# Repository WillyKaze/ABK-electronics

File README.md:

```
____ ___  _  _    ____ _    ____ ____ ___ ____ ____ _  _ _ ____ ____ 
|__| |__] |_/  __ |___ |    |___ |     |  |__/ |  | |\ | | |    [__  
|  | |__] | \_    |___ |___ |___ |___  |  |  \ |__| | \| | |___ ___] 
                                                                      
```

# Abrakabuki electronics

This repo contains all necessary files to design and produce PCBs for the Abrakabuki product range.

## File format and folder structure

Documentation files should be in PDF. Board image files can be in PNG or PDF.

PCB Design file are in EAGLE Standard edition (7.4) file format.

These are general rules to help maintain a consistent folder structure:

* All libraries are placed inside the shared libraries repository. It can be found
  on [Github](https://github.com/exmchina-dev/eagle-resources)  

* One board for each project folder.  

* Mutiples revisions can be placed inside a subfolder. i.e. ECS-Board/Rev A1  

* BOMs, partlists, spreadsheet should placed inside a BOMs/ folder.  

* Documentations files are in eagle-resources/doc or in doc/ inside a project folder.

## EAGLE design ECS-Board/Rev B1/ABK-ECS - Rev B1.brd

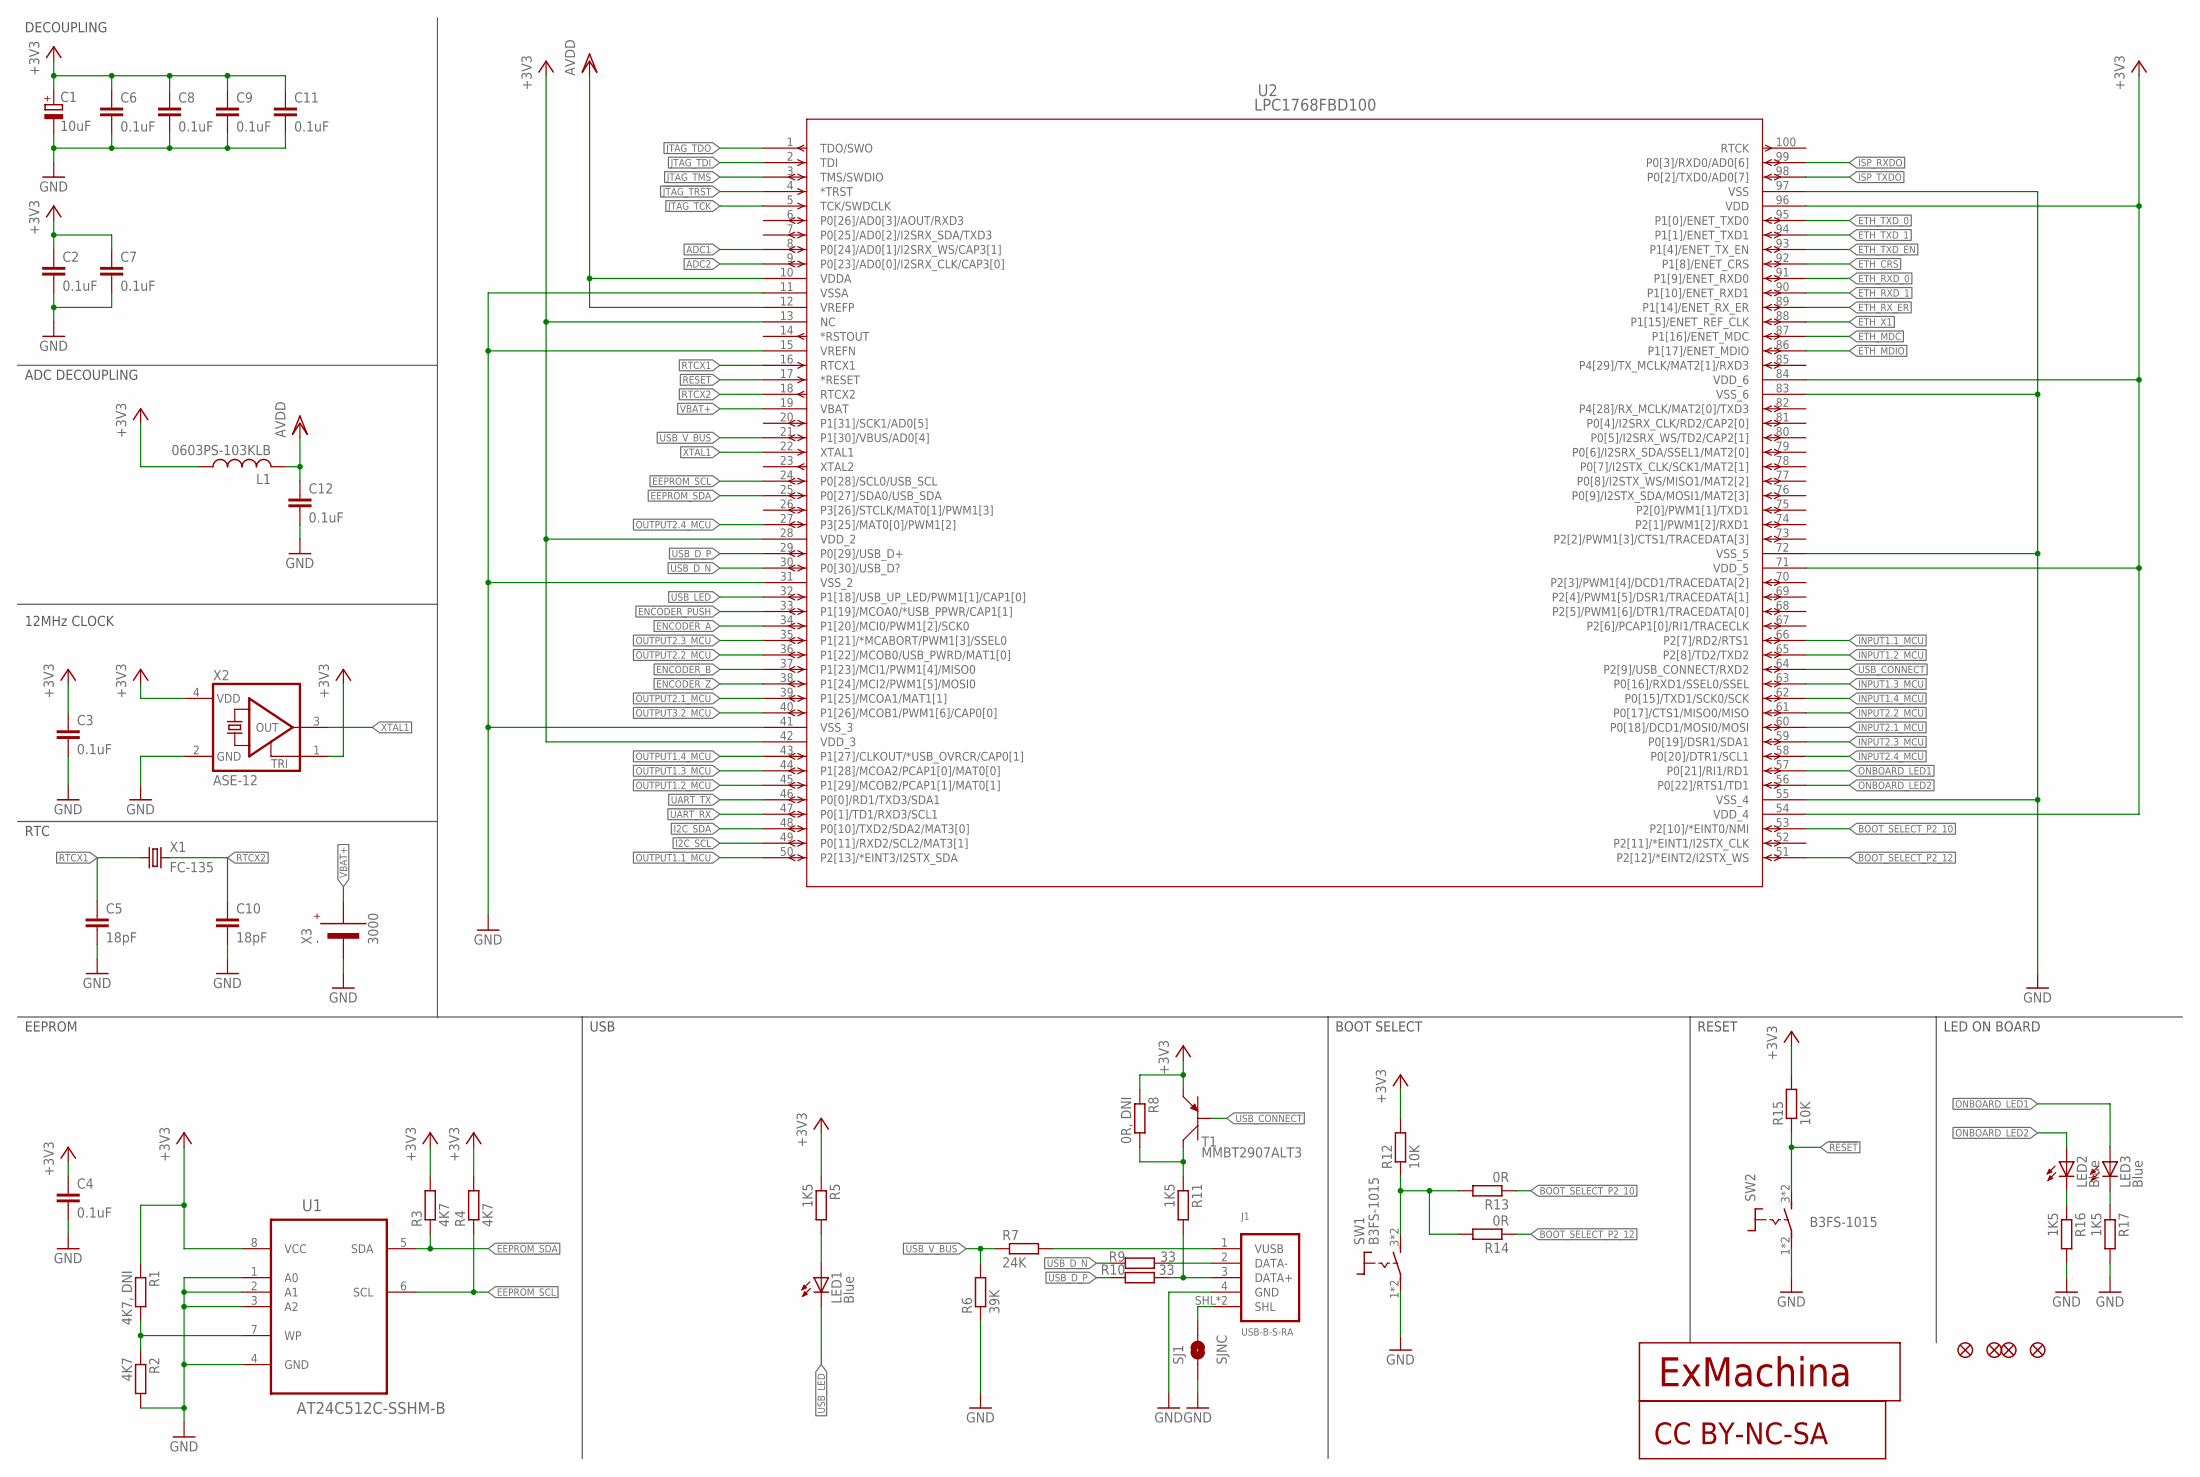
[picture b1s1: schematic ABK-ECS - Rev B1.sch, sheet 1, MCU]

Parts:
C1: 10uF; CT3216; MPN F931A106MAA
C2, C3, C4, C6, C7, C8, C9, C11, C12: 0.1uF; C0603; MPN MC0603B104K160CT
C5, C10: 18pF; C0603; MPN GRM1885C1H180JA01D
CC1: CC-BY-NC-SA
J1: USB-B-S-RA; MPN USB-B-S-RA
JP1, JP2, JP3, JP4: FIDUCIAL1X2; FIDUCIAL-1X2
L1: 0603PS-103KLB; 0603
LED1, LED2, LED3: Blue; CHIPLED_0603; MPN OVS-0603
R1: 4K7, DNI; R0603; MPN RC0603FR-074K7L
R2, R3, R4: 4K7; R0603; MPN RC0603FR-074K7L
R5, R11, R16, R17: 1K5; R0603; MPN RC0603FR-071K5L
R6: 39K; R0603
R7: 24K; R0603
R8: 0R, DNI; R0603; MPN RC0603FR-070RL
R9, R10: 33; R0603; MPN RC0603FR-0733RL
R12, R15: 10K; R0603; MPN RC0603FR-0710KL
R13, R14: 0R; R0603; MPN RC0603FR-070RL
SJ1: SJNC; SJ_2S
SW1, SW2: B3FS-1015; B3FS; MPN B3FS-1010
T1: MMBT2907ALT3; SOT−23
T2: EXMACHINA-LOGO-NAME; EXM-LOGO-BASELINE
U1: AT24C512C-SSHM-B; SOIC127P600X175-8N; MPN AT24C512C-SSHM-B
U2: LPC1768FBD100; SOT407-1; MPN LPC1768FBD100
X1: FC-135; MPN Q13FC13500004
X2: ASE-12; ASE; MPN ASE-12.000MHZ-LC-T
X3: 3000; MPN 3000

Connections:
!JTAG_TRST: U2.4 (*TRST)
!RESET: R15.1, SW2.3 (1), SW2.4 (1), U2.17 (*RESET); also elsewhere on the board
+3V3: C1.+, C2.1, C3.1, C4.1, C6.1, C7.1, C8.1, C9.1, C11.1, L1.P$1 (1), R1.1, R3.2, R4.2, R5.1, R8.1, R12.2, R15.2, T1.3 (C), U1.8 (VCC), U2.13 (NC), U2.28 (VDD_2), U2.42 (VDD_3), U2.54 (VDD_4), U2.71 (VDD_5), U2.84 (VDD_6), U2.96 (VDD), X2.1 (TRI), X2.4 (VDD); also elsewhere on the board
ADC1: U2.8 (P0[24]/AD0[1]/I2SRX_WS/CAP3[1]); also elsewhere on the board
ADC2: U2.9 (P0[23]/AD0[0]/I2SRX_CLK/CAP3[0]); also elsewhere on the board
AVDD: C12.1, L1.P$2 (2), U2.10 (VDDA), U2.12 (VREFP); also elsewhere on the board
BOOT_SELECT_P2_10: R13.1, U2.53 (P2[10]/*EINT0/NMI); also elsewhere on the board
BOOT_SELECT_P2_12: R14.1, U2.51 (P2[12]/*EINT2/I2STX_WS)
EEPROM_SCL: R4.1, U1.6 (SCL), U2.24 (P0[28]/SCL0/USB_SCL)
EEPROM_SDA: R3.1, U1.5 (SDA), U2.25 (P0[27]/SDA0/USB_SDA)
ENCODER_A: U2.34 (P1[20]/MCI0/PWM1[2]/SCK0); also elsewhere on the board
ENCODER_B: U2.37 (P1[23]/MCI1/PWM1[4]/MISO0); also elsewhere on the board
ENCODER_PUSH: U2.33 (P1[19]/MCOA0/*USB_PPWR/CAP1[1]); also elsewhere on the board
ENCODER_Z: U2.38 (P1[24]/MCI2/PWM1[5]/MOSI0); also elsewhere on the board
ETH_CRS: U2.92 (P1[8]/ENET_CRS); also elsewhere on the board
ETH_MDC: U2.87 (P1[16]/ENET_MDC); also elsewhere on the board
ETH_MDIO: U2.86 (P1[17]/ENET_MDIO); also elsewhere on the board
ETH_RXD_0: U2.91 (P1[9]/ENET_RXD0); also elsewhere on the board
ETH_RXD_1: U2.90 (P1[10]/ENET_RXD1); also elsewhere on the board
ETH_RX_ER: U2.89 (P1[14]/ENET_RX_ER); also elsewhere on the board
ETH_TXD_0: U2.95 (P1[0]/ENET_TXD0); also elsewhere on the board
ETH_TXD_1: U2.94 (P1[1]/ENET_TXD1); also elsewhere on the board
ETH_TXD_EN: U2.93 (P1[4]/ENET_TX_EN); also elsewhere on the board
ETH_X1: U2.88 (P1[15]/ENET_REF_CLK); also elsewhere on the board
GND: C1.-, C2.2, C3.2, C4.2, C5.2, C6.2, C7.2, C8.2, C9.2, C10.2, C11.2, C12.2, J1.4 (GND), R2.2, R6.1, R16.2, R17.2, SJ1.1, SW1.1 (2), SW1.2, SW2.1 (2), SW2.2, U1.1 (A0), U1.2 (A1), U1.3 (A2), U1.4 (GND), U2.11 (VSSA), U2.15 (VREFN), U2.31 (VSS_2), U2.41 (VSS_3), U2.55 (VSS_4), U2.72 (VSS_5), U2.83 (VSS_6), U2.97 (VSS), X2.2 (GND), X3.- (VBAT-); also elsewhere on the board
I2C_SCL: U2.49 (P0[11]/RXD2/SCL2/MAT3[1]); also elsewhere on the board
I2C_SDA: U2.48 (P0[10]/TXD2/SDA2/MAT3[0]); also elsewhere on the board
INPUT1.1_MCU: U2.66 (P2[7]/RD2/RTS1); also elsewhere on the board
INPUT1.2_MCU: U2.65 (P2[8]/TD2/TXD2); also elsewhere on the board
INPUT1.3_MCU: U2.63 (P0[16]/RXD1/SSEL0/SSEL); also elsewhere on the board
INPUT1.4_MCU: U2.62 (P0[15]/TXD1/SCK0/SCK); also elsewhere on the board
INPUT2.1_MCU: U2.60 (P0[18]/DCD1/MOSI0/MOSI); also elsewhere on the board
INPUT2.2_MCU: U2.61 (P0[17]/CTS1/MISO0/MISO); also elsewhere on the board
INPUT2.3_MCU: U2.59 (P0[19]/DSR1/SDA1); also elsewhere on the board
INPUT2.4_MCU: U2.58 (P0[20]/DTR1/SCL1); also elsewhere on the board
ISP_RXDO: U2.99 (P0[3]/RXD0/AD0[6]); also elsewhere on the board
ISP_TXDO: U2.98 (P0[2]/TXD0/AD0[7]); also elsewhere on the board
JTAG_TCK: U2.5 (TCK/SWDCLK); also elsewhere on the board
JTAG_TDI: U2.2 (TDI); also elsewhere on the board
JTAG_TDO: U2.1 (TDO/SWO); also elsewhere on the board
JTAG_TMS: U2.3 (TMS/SWDIO); also elsewhere on the board
unnamed: J1.3 (DATA+), R10.1, R11.2
unnamed: J1.2 (DATA-), R9.1
unnamed: LED3.C, R17.1
unnamed: R12.1, R13.2, R14.2, SW1.3 (1), SW1.4 (1)
unnamed: R1.2, R2.1, U1.7 (WP)
unnamed: LED1.A, R5.2
unnamed: LED2.C, R16.1
unnamed: R8.2, R11.1, T1.2 (E)
unnamed: J1.SHL, J1.SHL1 (SHL), SJ1.2
unnamed: J1.1 (VUSB), R7.2
ONBOARD_LED1: LED3.A, U2.57 (P0[21]/RI1/RD1)
ONBOARD_LED2: LED2.A, U2.56 (P0[22]/RTS1/TD1)
OUTPUT1.1_MCU: U2.50 (P2[13]/*EINT3/I2STX_SDA); also elsewhere on the board
OUTPUT1.2_MCU: U2.45 (P1[29]/MCOB2/PCAP1[1]/MAT0[1]); also elsewhere on the board
OUTPUT1.3_MCU: U2.44 (P1[28]/MCOA2/PCAP1[0]/MAT0[0]); also elsewhere on the board
OUTPUT1.4_MCU: U2.43 (P1[27]/CLKOUT/*USB_OVRCR/CAP0[1]); also elsewhere on the board
OUTPUT2.1_MCU: U2.39 (P1[25]/MCOA1/MAT1[1]); also elsewhere on the board
OUTPUT2.2_MCU: U2.36 (P1[22]/MCOB0/USB_PWRD/MAT1[0]); also elsewhere on the board
OUTPUT2.3_MCU: U2.35 (P1[21]/*MCABORT/PWM1[3]/SSEL0); also elsewhere on the board
OUTPUT2.4_MCU: U2.27 (P3[25]/MAT0[0]/PWM1[2]); also elsewhere on the board
OUTPUT3.2_MCU: U2.40 (P1[26]/MCOB1/PWM1[6]/CAP0[0]); also elsewhere on the board
RTCX1: C5.1, U2.16 (RTCX1), X1.1
RTCX2: C10.1, U2.18 (RTCX2), X1.2
UART_RX: U2.47 (P0[1]/TD1/RXD3/SCL1); also elsewhere on the board
UART_TX: U2.46 (P0[0]/RD1/TXD3/SDA1); also elsewhere on the board
USB_CONNECT: T1.1 (B), U2.64 (P2[9]/USB_CONNECT/RXD2)
USB_D_N: R9.2, U2.30 (P0[30]/USB_D?)
USB_D_P: R10.2, U2.29 (P0[29]/USB_D+)
USB_LED: LED1.C, U2.32 (P1[18]/USB_UP_LED/PWM1[1]/CAP1[0])
USB_V_BUS: R6.2, R7.1, U2.21 (P1[30]/VBUS/AD0[4])
VBAT+: U2.19 (VBAT), X3.+1 (VBAT+), X3.+2 (VBAT+)
XTAL1: U2.22 (XTAL1), X2.3 (OUT)

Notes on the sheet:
USB
BOOT SELECT
LED ON BOARD
RESET
EEPROM
RTC
12MHz CLOCK
DECOUPLING
ADC DECOUPLING

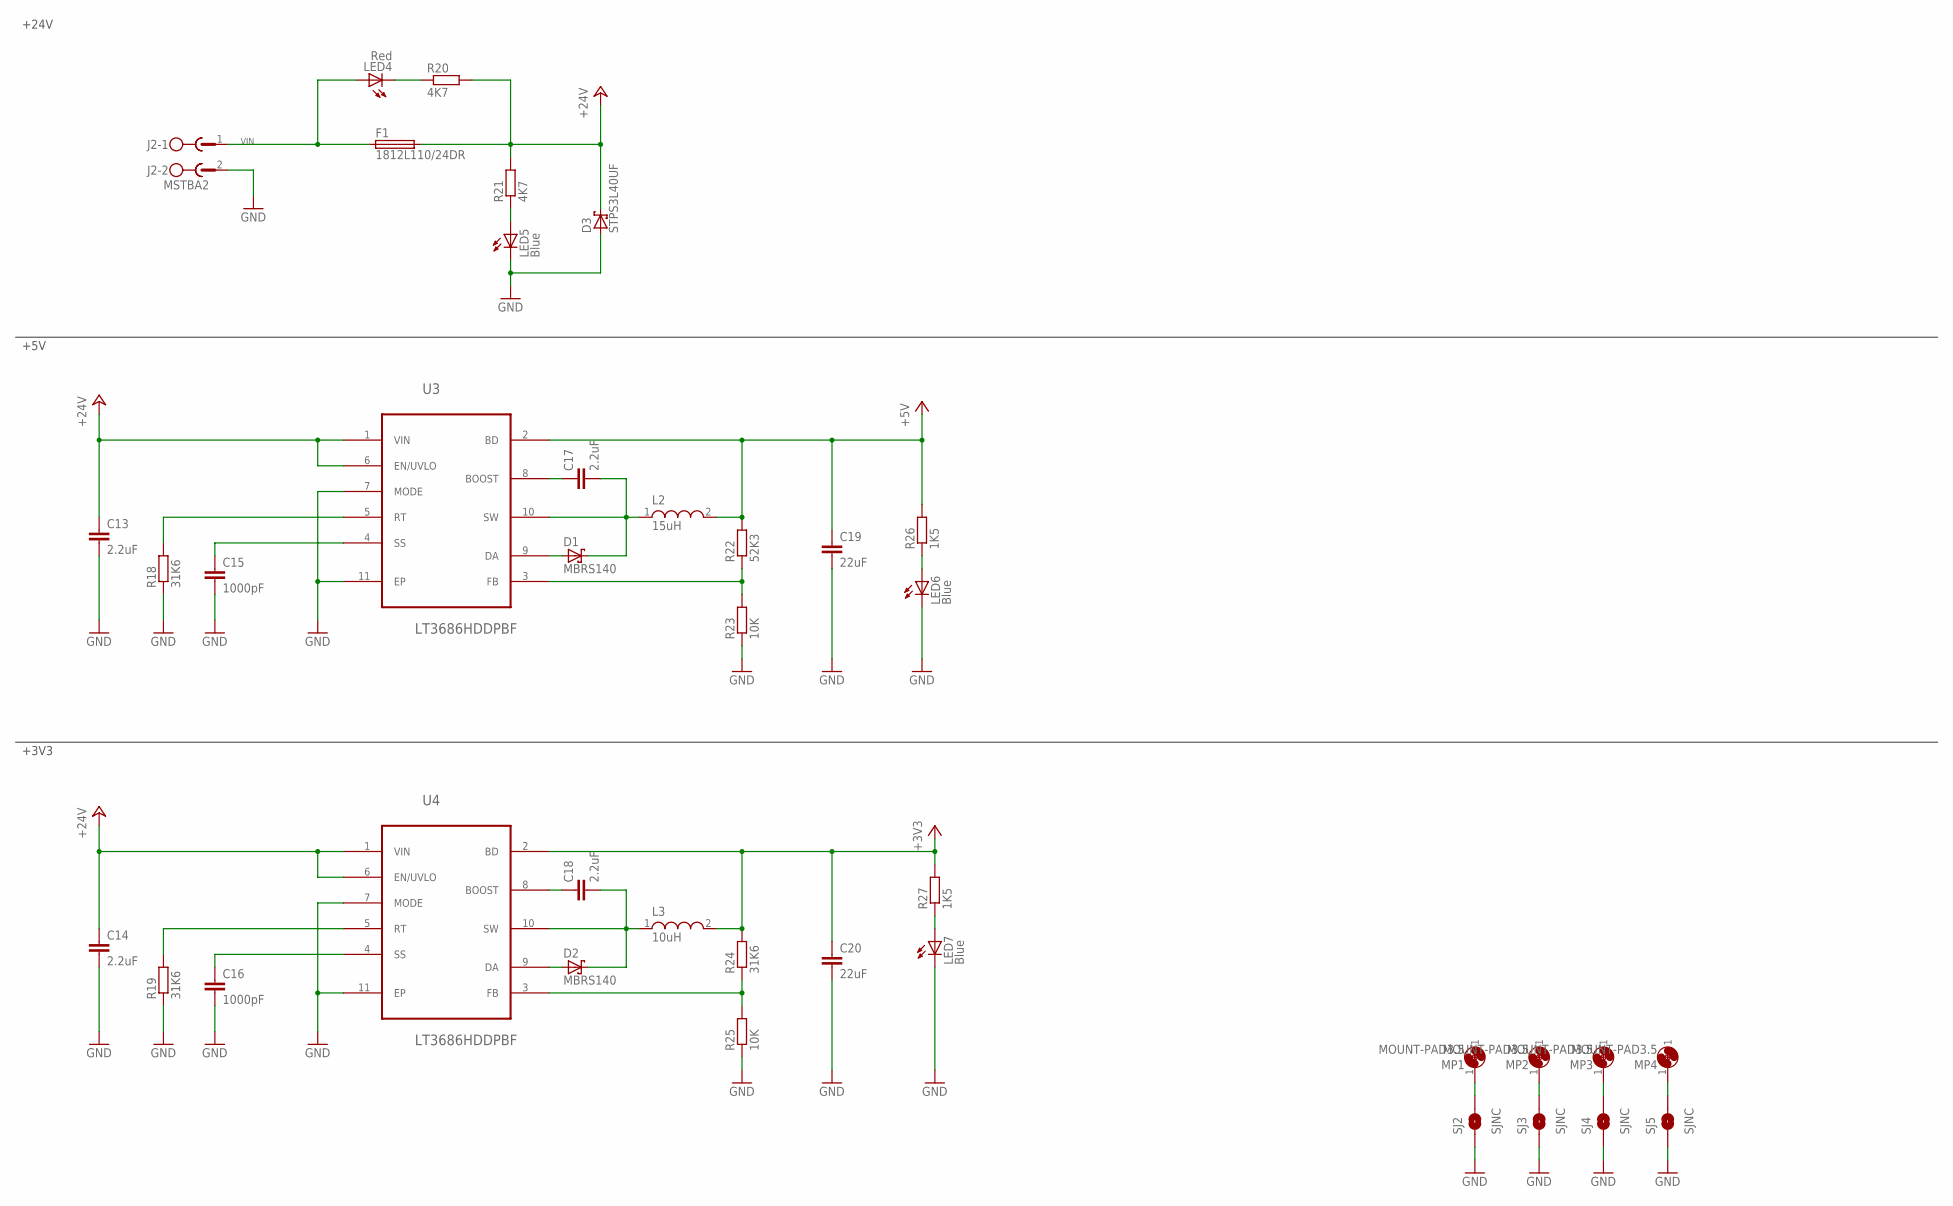
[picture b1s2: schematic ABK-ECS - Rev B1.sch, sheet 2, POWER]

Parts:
C13, C14, C17, C18: 2.2uF; C0603; MPN GRT188R61H225KE13D
C15, C16: 1000pF; C0603; MPN GRM188R71H102KA01D
C19, C20: 22uF; C0805; MPN C0805C226M9PACTU
D1, D2: MBRS140; DO-214AA; MPN MBRS140T3G
D3: STPS3L40UF; SMB
F1: 1812L110/24DR; LITTLEFUSE_SMD; MPN 3557
J2: MSTBA2
L2: 15uH; WE-PD2_5848/5820; MPN 744774115
L3: 10uH; WE-PD2_5848/5820; MPN 74477410
LED4: Red; CHIPLED_0603; MPN OVS-0608
LED5, LED6, LED7: Blue; CHIPLED_0603; MPN OVS-0603
MP1, MP2, MP3, MP4: MOUNT-PAD3.5; P3,5
R18, R19, R24: 31K6; R0603; MPN MCMR06X3162FTL
R20, R21: 4K7; R0603; MPN RC0603FR-074K7L
R22: 52K3; R0603; MPN MC0063W0603152K3
R23, R25: 10K; R0603; MPN RC0603FR-0710KL
R26, R27: 1K5; R0603; MPN RC0603FR-071K5L
SJ2, SJ3, SJ4, SJ5: SJNC; SJ_2S
U3, U4: LT3686HDDPBF; DFN300X300X80-11N

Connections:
1: MP1.1, SJ2.2
2: MP2.1, SJ3.2
3: MP3.1, SJ4.2
4: MP4.1, SJ5.2
+3V3: C20.1, L3.2, R24.2, R27.2, U4.2 (BD); also elsewhere on the board
+5V: C19.1, L2.2, R22.2, R26.2, U3.2 (BD); also elsewhere on the board
+24V: C13.1, C14.1, D3.C, F1.2, R20.2, R21.2, U3.1 (VIN), U3.6 (EN/UVLO), U4.1 (VIN), U4.6 (EN/UVLO); also elsewhere on the board
GND: C13.2, C14.2, C15.2, C16.2, C19.2, C20.2, D3.A, J2.2, LED5.C, LED6.C, LED7.C, R18.1, R19.1, R23.1, R25.1, SJ2.1, SJ3.1, SJ4.1, SJ5.1, U3.7 (MODE), U3.11 (EP), U4.7 (MODE), U4.11 (EP); also elsewhere on the board
unnamed: R18.2, U3.5 (RT)
unnamed: C15.1, U3.4 (SS)
unnamed: R19.2, U4.5 (RT)
unnamed: C16.1, U4.4 (SS)
unnamed: R22.1, R23.2, U3.3 (FB)
unnamed: C17.1, U3.8 (BOOST)
unnamed: C17.2, D1.C, L2.1, U3.10 (SW)
unnamed: D1.A, U3.9 (DA)
unnamed: R24.1, R25.2, U4.3 (FB)
unnamed: C18.1, U4.8 (BOOST)
unnamed: C18.2, D2.C, L3.1, U4.10 (SW)
unnamed: D2.A, U4.9 (DA)
unnamed: LED5.A, R21.1
unnamed: LED4.C, R20.1
unnamed: LED7.A, R27.1
unnamed: LED6.A, R26.1
VIN: F1.1, J2.1, LED4.A

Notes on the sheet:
+5V
+3V3
+24V

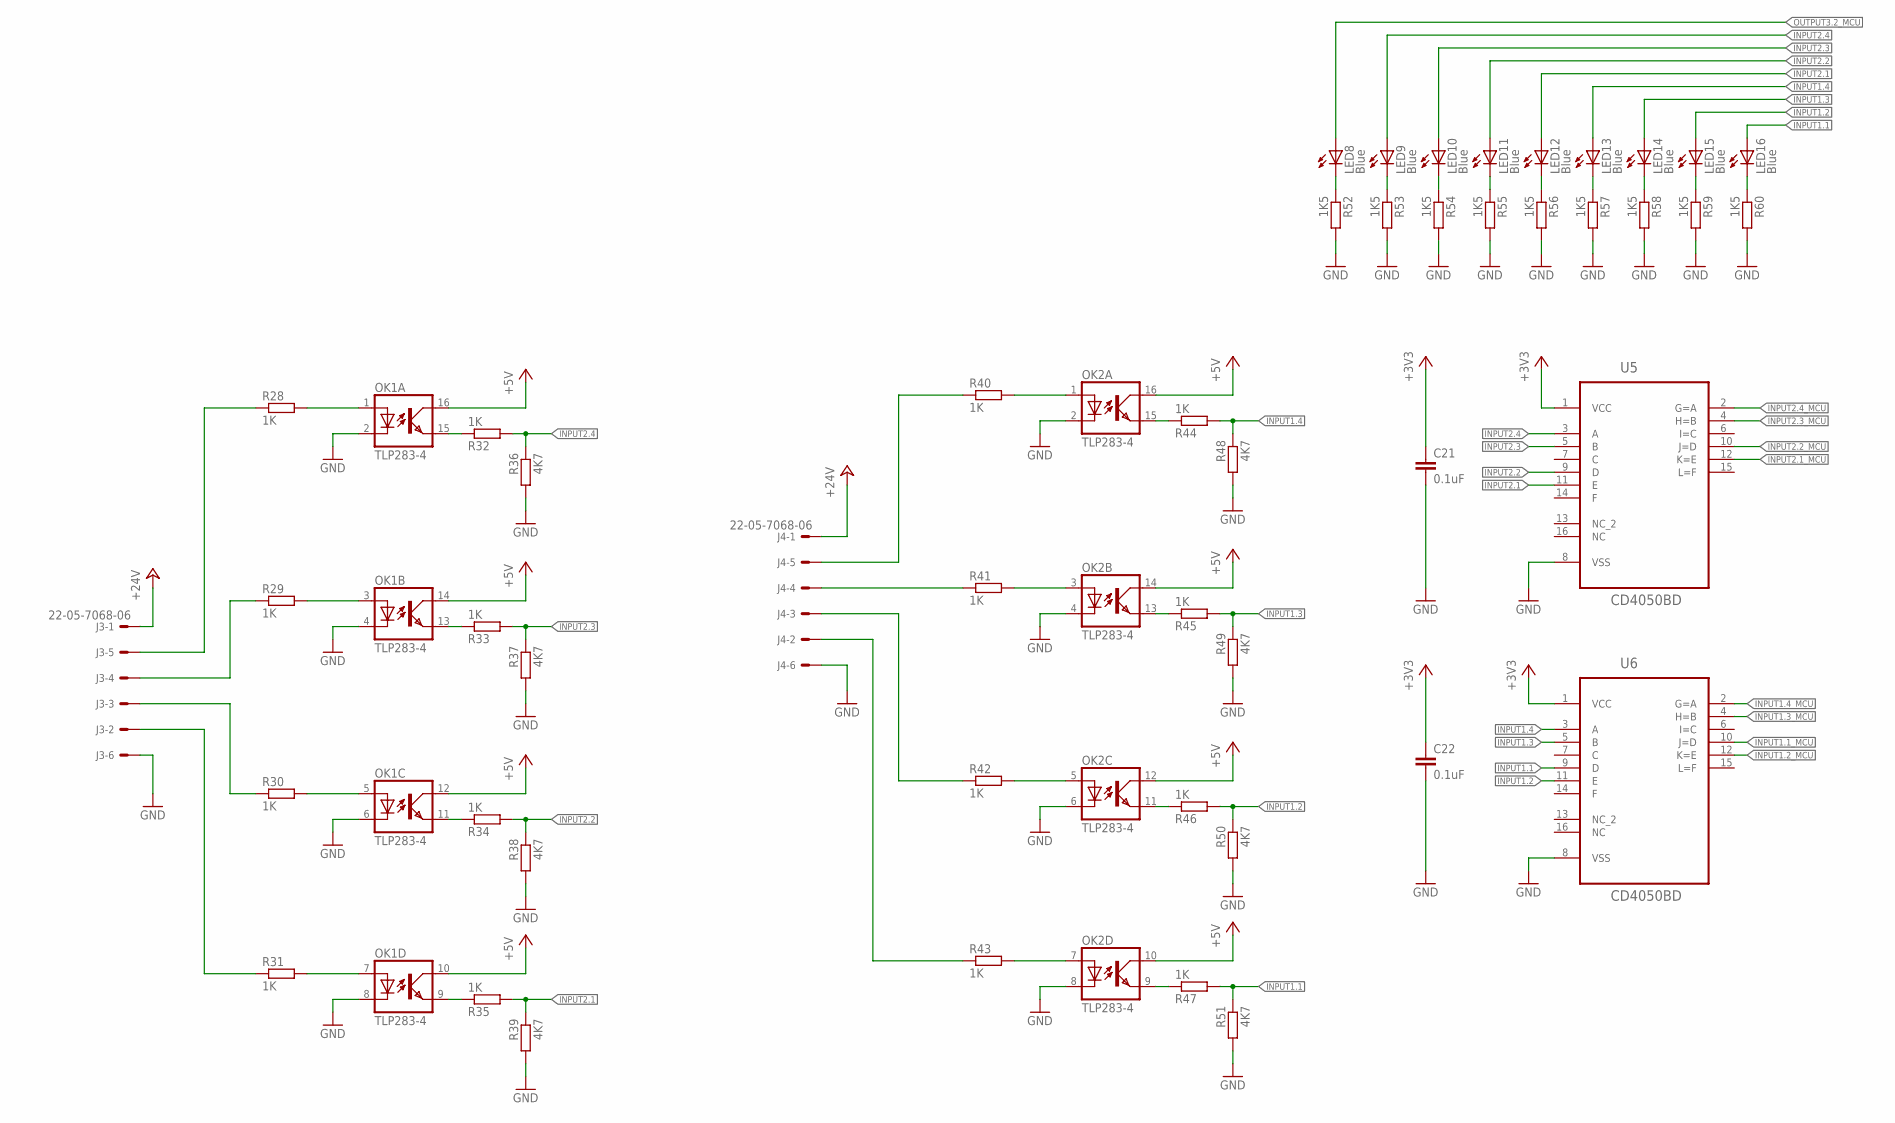
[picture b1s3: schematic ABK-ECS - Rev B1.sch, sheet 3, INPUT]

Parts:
C21, C22: 0.1uF; C0603; MPN MC0603B104K160CT
J3, J4: 22-05-7068-06; 7395-06
LED8, LED9, LED10, LED11, LED12, LED13, LED14, LED15, LED16: Blue; CHIPLED_0603; MPN OVS-0603
OK1, OK2: TLP283-4; MINI-FLAT-16; MPN TCMT4100
R28, R29, R30, R31, R32, R33, R34, R35, R40, R41, R42, R43, R44, R45, R46, R47: 1K; R0603; MPN RC0603FR-071KL
R36, R37, R38, R39, R48, R49, R50, R51: 4K7; R0603; MPN RC0603FR-074K7L
R52, R53, R54, R55, R56, R57, R58, R59, R60: 1K5; R0603; MPN RC0603FR-071K5L
U5, U6: CD4050BD; SOIC127P600X175-16N

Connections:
+3V3: C21.1, C22.1, U5.1 (VCC), U6.1 (VCC); also elsewhere on the board
+5V: OK1.10 (COL), OK1.12 (COL), OK1.14 (COL), OK1.16 (COL), OK2.10 (COL), OK2.12 (COL), OK2.14 (COL), OK2.16 (COL); also elsewhere on the board
+24V: J3.1, J4.1; also elsewhere on the board
GND: C21.2, C22.2, J3.6, J4.6, OK1.2 (C), OK1.4 (C), OK1.6 (C), OK1.8 (C), OK2.2 (C), OK2.4 (C), OK2.6 (C), OK2.8 (C), R36.2, R37.2, R38.2, R39.2, R48.2, R49.2, R50.2, R51.2, R52.2, R53.2, R54.2, R55.2, R56.2, R57.2, R58.2, R59.2, R60.2, U5.8 (VSS), U6.8 (VSS); also elsewhere on the board
INPUT1.1: LED16.A, R47.2, R51.1, U6.9 (D)
INPUT1.1_MCU: U6.10 (J=D); also elsewhere on the board
INPUT1.2: LED15.A, R46.2, R50.1, U6.11 (E)
INPUT1.2_MCU: U6.12 (K=E); also elsewhere on the board
INPUT1.3: LED14.A, R45.2, R49.1, U6.5 (B)
INPUT1.3_MCU: U6.4 (H=B); also elsewhere on the board
INPUT1.4: LED13.A, R44.2, R48.1, U6.3 (A)
INPUT1.4_MCU: U6.2 (G=A); also elsewhere on the board
INPUT2.1: LED12.A, R35.2, R39.1, U5.11 (E)
INPUT2.1_MCU: U5.12 (K=E); also elsewhere on the board
INPUT2.2: LED11.A, R34.2, R38.1, U5.9 (D)
INPUT2.2_MCU: U5.10 (J=D); also elsewhere on the board
INPUT2.3: LED10.A, R33.2, R37.1, U5.5 (B)
INPUT2.3_MCU: U5.4 (H=B); also elsewhere on the board
INPUT2.4: LED9.A, R32.2, R36.1, U5.3 (A)
INPUT2.4_MCU: U5.2 (G=A); also elsewhere on the board
unnamed: OK1.1 (A), R28.2
unnamed: OK1.3 (A), R29.2
unnamed: OK1.5 (A), R30.2
unnamed: OK1.7 (A), R31.2
unnamed: J3.2, R31.1
unnamed: J3.3, R30.1
unnamed: J3.4, R29.1
unnamed: J3.5, R28.1
unnamed: LED8.C, R52.1
unnamed: LED9.C, R53.1
unnamed: LED10.C, R54.1
unnamed: LED11.C, R55.1
unnamed: OK1.9 (EMIT), R35.1
unnamed: OK1.11 (EMIT), R34.1
unnamed: OK1.13 (EMIT), R33.1
unnamed: OK1.15 (EMIT), R32.1
unnamed: LED12.C, R56.1
unnamed: OK2.1 (A), R40.2
unnamed: J4.5, R40.1
unnamed: LED16.C, R60.1
unnamed: OK2.15 (EMIT), R44.1
unnamed: OK2.3 (A), R41.2
unnamed: J4.4, R41.1
unnamed: OK2.13 (EMIT), R45.1
unnamed: OK2.5 (A), R42.2
unnamed: J4.3, R42.1
unnamed: OK2.11 (EMIT), R46.1
unnamed: LED13.C, R57.1
unnamed: LED14.C, R58.1
unnamed: LED15.C, R59.1
unnamed: OK2.9 (EMIT), R47.1
unnamed: OK2.7 (A), R43.2
unnamed: J4.2, R43.1
OUTPUT3.2_MCU: LED8.A; also elsewhere on the board

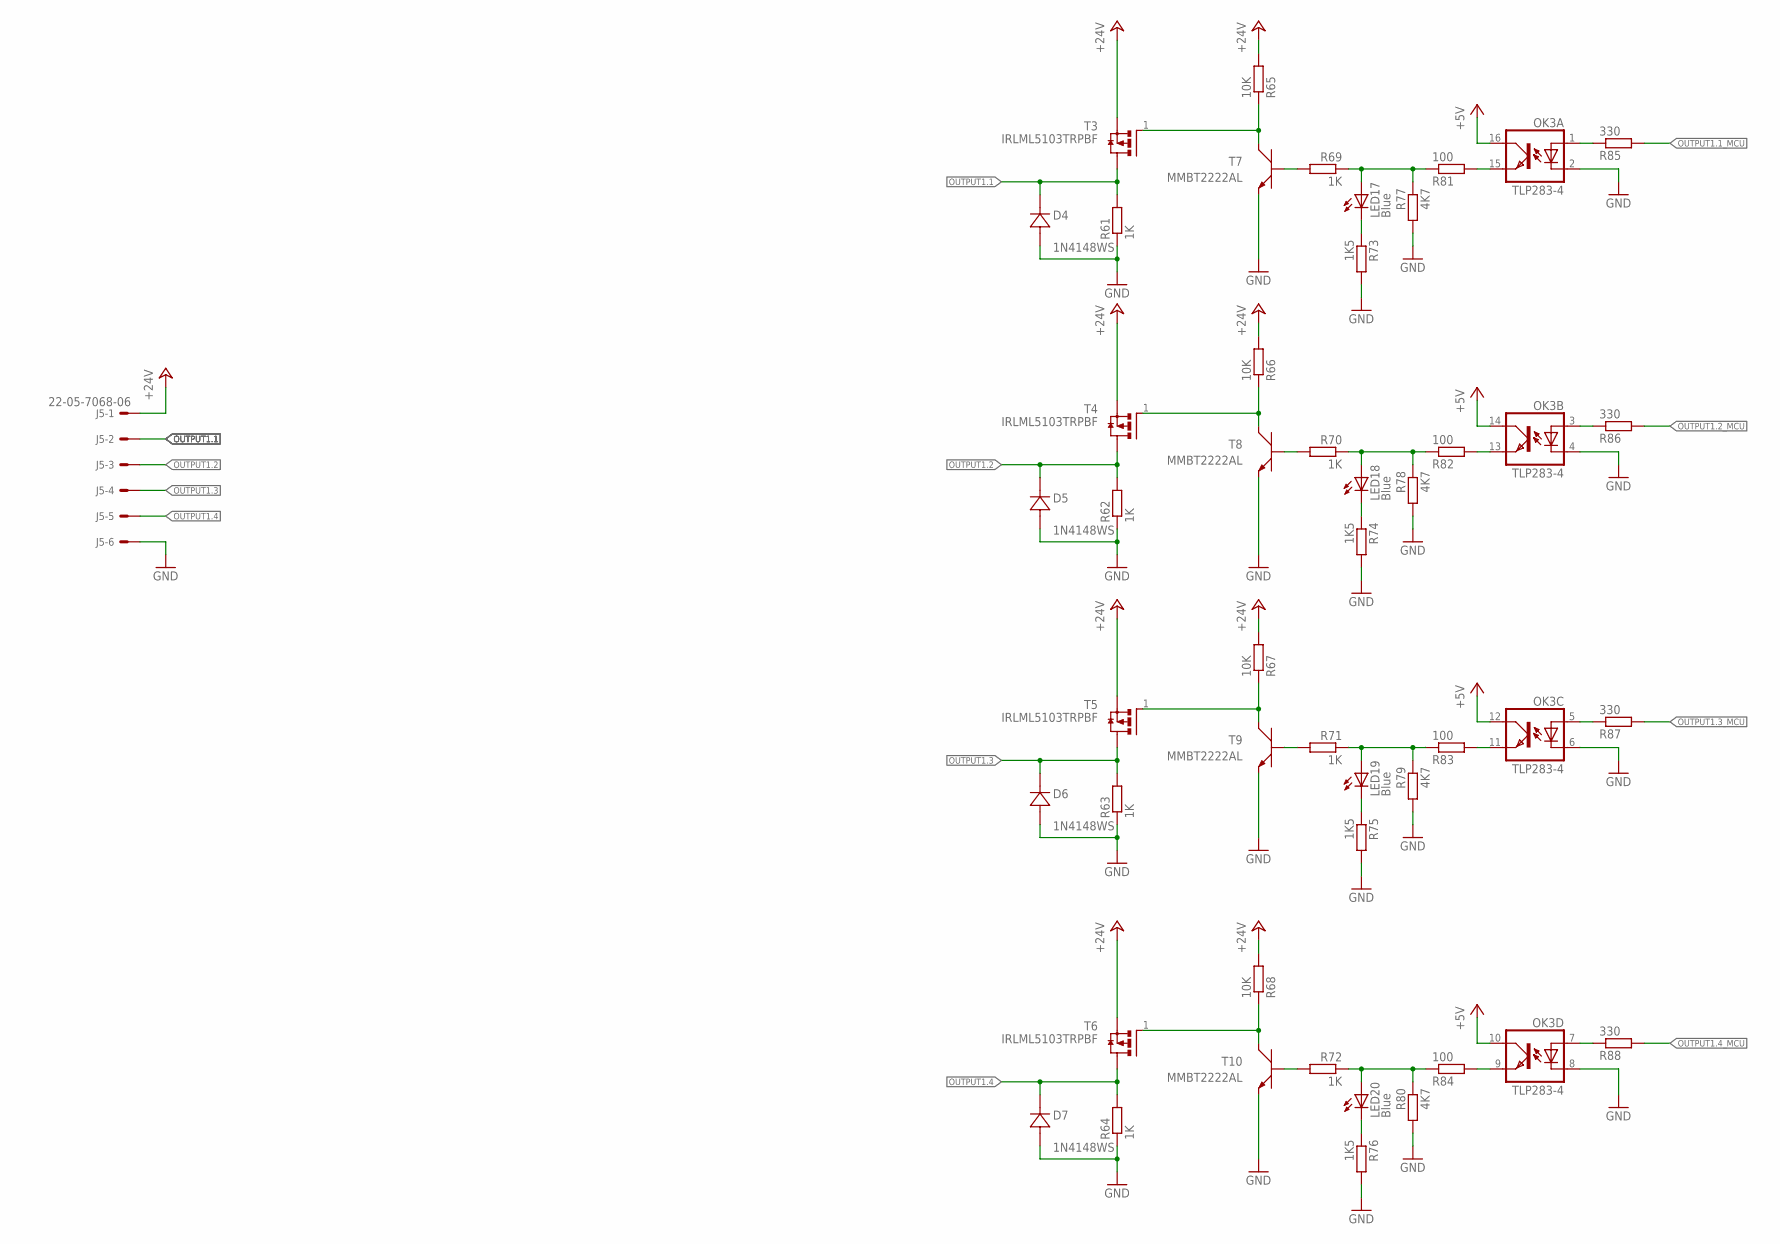
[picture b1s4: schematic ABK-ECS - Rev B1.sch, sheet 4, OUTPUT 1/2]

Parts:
D4, D5, D6, D7: 1N4148WS; SOD323-W; MPN 1N4148WS
J5: 22-05-7068-06; 7395-06
LED17, LED18, LED19, LED20: Blue; CHIPLED_0603; MPN OVS-0603
OK3: TLP283-4; MINI-FLAT-16; MPN TCMT4100
R61, R62, R63, R64: 1K; R1206
R65, R66, R67, R68: 10K; R0603; MPN RC0603FR-0710KL
R69, R70, R71, R72: 1K; R0603; MPN RC0603FR-071KL
R73, R74, R75, R76: 1K5; R0603; MPN RC0603FR-071K5L
R77, R78, R79, R80: 4K7; R0603; MPN RC0603FR-074K7L
R81, R82, R83, R84: 100; R0603; MPN RC0603FR-13100RL
R85, R86, R87, R88: 330; R0603; MPN RC0603FR-07330RL
T3, T4, T5, T6: IRLML5103TRPBF; SOT95P240X112-3N; MPN IRLML5103TRPBF
T7, T8, T9, T10: MMBT2222AL; SOT−23; MPN MMBT2222ALT1G

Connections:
+5V: OK3.10 (COL), OK3.12 (COL), OK3.14 (COL), OK3.16 (COL); also elsewhere on the board
+24V: J5.1, R65.2, R66.2, R67.2, R68.2, T3.2 (S), T4.2 (S), T5.2 (S), T6.2 (S); also elsewhere on the board
GND: D4.A (2), D5.A (2), D6.A (2), D7.A (2), J5.6, OK3.2 (C), OK3.4 (C), OK3.6 (C), OK3.8 (C), R61.1, R62.1, R63.1, R64.1, R73.2, R74.2, R75.2, R76.2, R77.2, R78.2, R79.2, R80.2, T7.2 (E), T8.2 (E), T9.2 (E), T10.2 (E); also elsewhere on the board
unnamed: LED17.A, R69.1, R77.1, R81.1
unnamed: OK3.15 (EMIT), R81.2
unnamed: LED18.A, R70.1, R78.1, R82.1
unnamed: OK3.13 (EMIT), R82.2
unnamed: LED19.A, R71.1, R79.1, R83.1
unnamed: LED20.A, R72.1, R80.1, R84.1
unnamed: OK3.11 (EMIT), R83.2
unnamed: OK3.9 (EMIT), R84.2
unnamed: OK3.1 (A), R85.1
unnamed: OK3.3 (A), R86.1
unnamed: OK3.7 (A), R88.1
unnamed: OK3.5 (A), R87.1
unnamed: LED17.C, R73.1
unnamed: LED18.C, R74.1
unnamed: LED19.C, R75.1
unnamed: LED20.C, R76.1
unnamed: R65.1, T3.1 (G), T7.3 (C)
unnamed: R66.1, T4.1 (G), T8.3 (C)
unnamed: R67.1, T5.1 (G), T9.3 (C)
unnamed: R68.1, T6.1 (G), T10.3 (C)
unnamed: R69.2, T7.1 (B)
unnamed: R70.2, T8.1 (B)
unnamed: R71.2, T9.1 (B)
unnamed: R72.2, T10.1 (B)
OUTPUT1.1: D4.C (1), J5.2, R61.2, T3.3 (D)
OUTPUT1.1_MCU: R85.2; also elsewhere on the board
OUTPUT1.2: D5.C (1), J5.3, R62.2, T4.3 (D)
OUTPUT1.2_MCU: R86.2; also elsewhere on the board
OUTPUT1.3: D6.C (1), J5.4, R63.2, T5.3 (D)
OUTPUT1.3_MCU: R87.2; also elsewhere on the board
OUTPUT1.4: D7.C (1), J5.5, R64.2, T6.3 (D)
OUTPUT1.4_MCU: R88.2; also elsewhere on the board

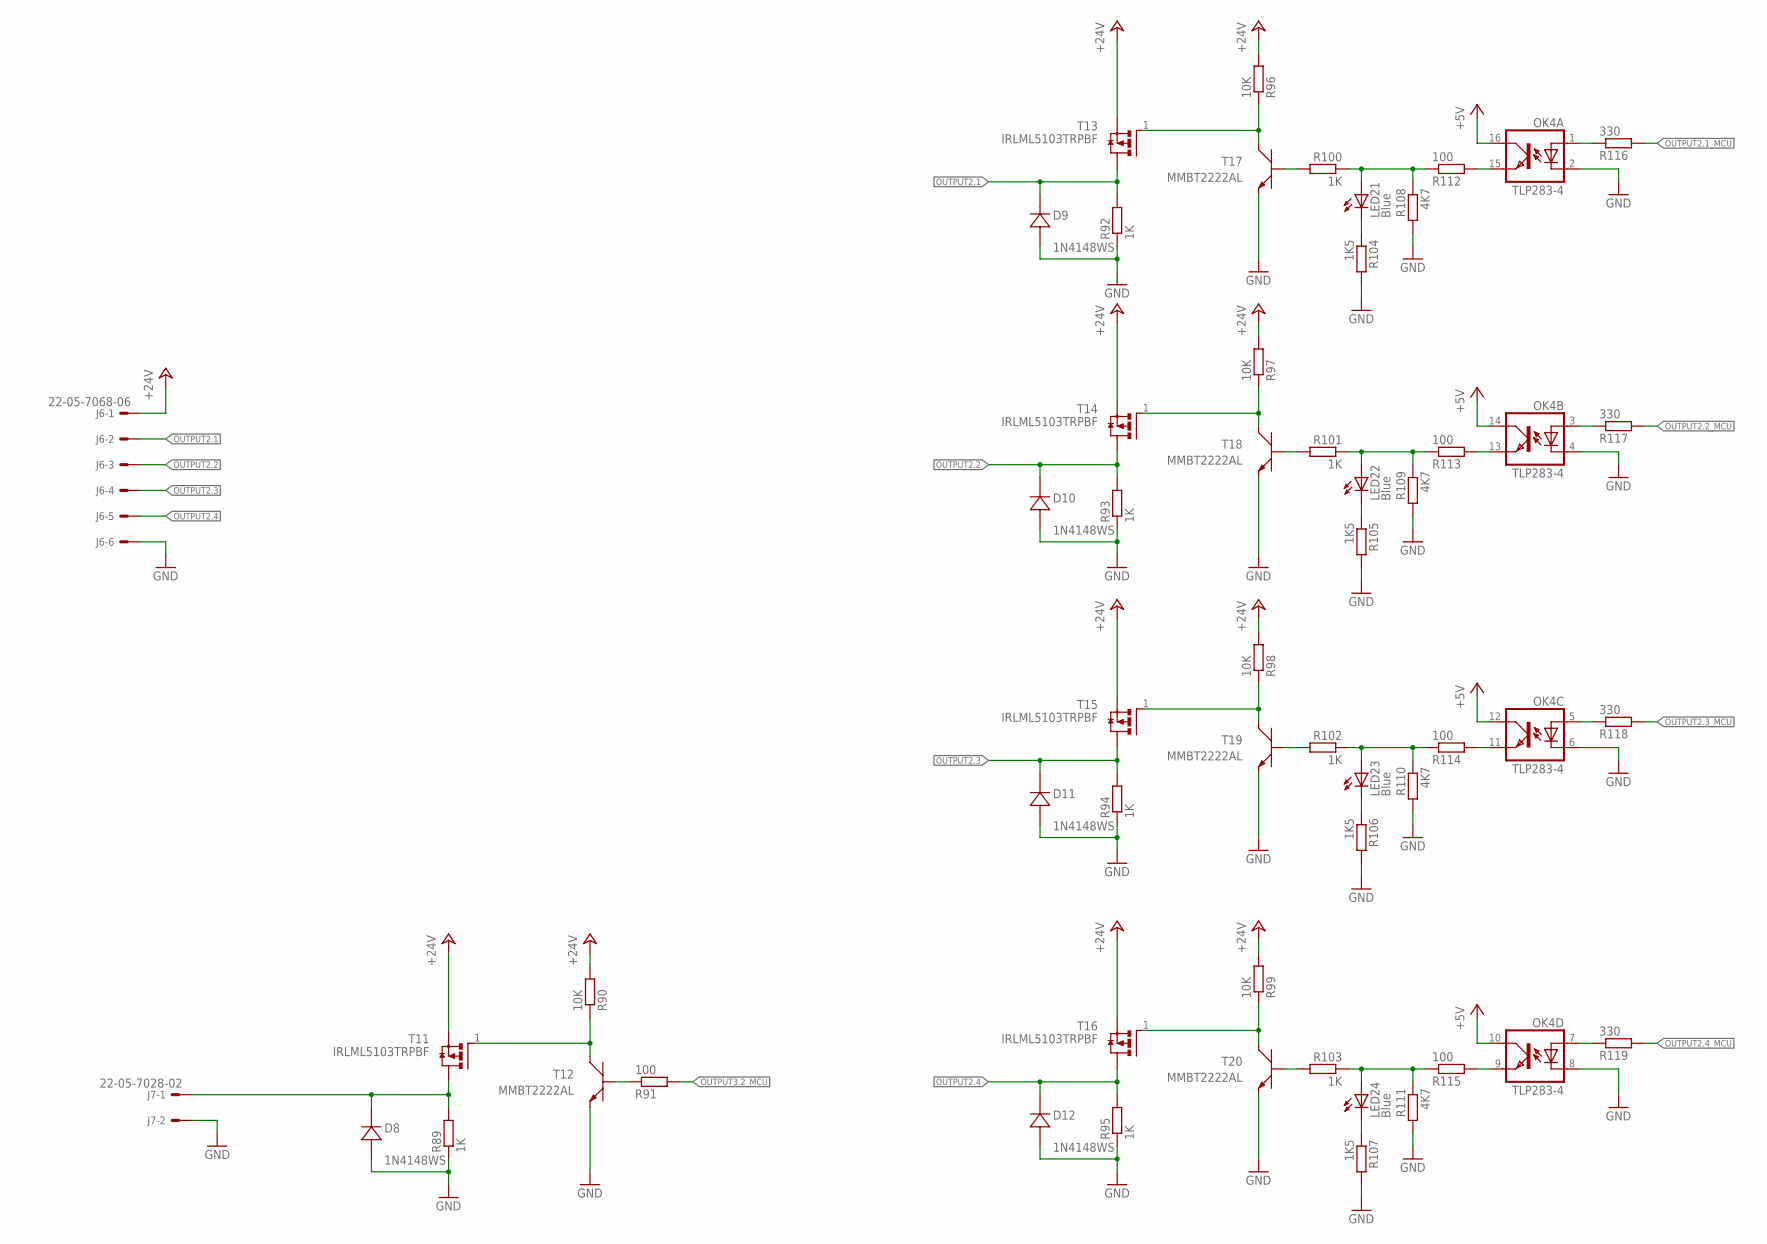
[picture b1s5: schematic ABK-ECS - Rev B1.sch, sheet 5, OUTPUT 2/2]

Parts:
D8, D9, D10, D11, D12: 1N4148WS; SOD323-W; MPN 1N4148WS
J6: 22-05-7068-06; 7395-06
J7: 22-05-7028-02; 7395-02; MPN 22-05-7028
LED21, LED22, LED23, LED24: Blue; CHIPLED_0603; MPN OVS-0603
OK4: TLP283-4; MINI-FLAT-16; MPN TCMT4100
R89, R92, R93, R94, R95: 1K; R1206
R90, R96, R97, R98, R99: 10K; R0603; MPN RC0603FR-0710KL
R91, R112, R113, R114, R115: 100; R0603; MPN RC0603FR-13100RL
R100, R101, R102, R103: 1K; R0603; MPN RC0603FR-071KL
R104, R105, R106, R107: 1K5; R0603; MPN RC0603FR-071K5L
R108, R109, R110, R111: 4K7; R0603; MPN RC0603FR-074K7L
R116, R117, R118, R119: 330; R0603; MPN RC0603FR-07330RL
T11, T13, T14, T15, T16: IRLML5103TRPBF; SOT95P240X112-3N; MPN IRLML5103TRPBF
T12, T17, T18, T19, T20: MMBT2222AL; SOT−23; MPN MMBT2222ALT1G

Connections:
+5V: OK4.10 (COL), OK4.12 (COL), OK4.14 (COL), OK4.16 (COL); also elsewhere on the board
+24V: J6.1, R90.2, R96.2, R97.2, R98.2, R99.2, T11.2 (S), T13.2 (S), T14.2 (S), T15.2 (S), T16.2 (S); also elsewhere on the board
GND: D8.A (2), D9.A (2), D10.A (2), D11.A (2), D12.A (2), J6.6, J7.2, OK4.2 (C), OK4.4 (C), OK4.6 (C), OK4.8 (C), R89.1, R92.1, R93.1, R94.1, R95.1, R104.2, R105.2, R106.2, R107.2, R108.2, R109.2, R110.2, R111.2, T12.2 (E), T17.2 (E), T18.2 (E), T19.2 (E), T20.2 (E); also elsewhere on the board
MOTOR_VFQ: D8.C (1), J7.1, R89.2, T11.3 (D)
unnamed: R100.2, T17.1 (B)
unnamed: R96.1, T13.1 (G), T17.3 (C)
unnamed: R101.2, T18.1 (B)
unnamed: R97.1, T14.1 (G), T18.3 (C)
unnamed: R102.2, T19.1 (B)
unnamed: R98.1, T15.1 (G), T19.3 (C)
unnamed: R103.2, T20.1 (B)
unnamed: R99.1, T16.1 (G), T20.3 (C)
unnamed: R91.1, T12.1 (B)
unnamed: R90.1, T11.1 (G), T12.3 (C)
unnamed: LED21.A, R100.1, R108.1, R112.1
unnamed: OK4.15 (EMIT), R112.2
unnamed: LED22.A, R101.1, R109.1, R113.1
unnamed: OK4.13 (EMIT), R113.2
unnamed: LED23.A, R102.1, R110.1, R114.1
unnamed: LED24.A, R103.1, R111.1, R115.1
unnamed: OK4.11 (EMIT), R114.2
unnamed: OK4.9 (EMIT), R115.2
unnamed: OK4.1 (A), R116.1
unnamed: OK4.3 (A), R117.1
unnamed: OK4.7 (A), R119.1
unnamed: OK4.5 (A), R118.1
unnamed: LED21.C, R104.1
unnamed: LED22.C, R105.1
unnamed: LED23.C, R106.1
unnamed: LED24.C, R107.1
OUTPUT2.1: D9.C (1), J6.2, R92.2, T13.3 (D)
OUTPUT2.1_MCU: R116.2; also elsewhere on the board
OUTPUT2.2: D10.C (1), J6.3, R93.2, T14.3 (D)
OUTPUT2.2_MCU: R117.2; also elsewhere on the board
OUTPUT2.3: D11.C (1), J6.4, R94.2, T15.3 (D)
OUTPUT2.3_MCU: R118.2; also elsewhere on the board
OUTPUT2.4: D12.C (1), J6.5, R95.2, T16.3 (D)
OUTPUT2.4_MCU: R119.2; also elsewhere on the board
OUTPUT3.2_MCU: R91.2; also elsewhere on the board

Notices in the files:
parts and their libraries:
NXP: COPYRIGHT: Copyright C 2015 Accelerated Designs. All rights reserved
Wurth-POWER_MAGNETICS-rev16f: Copyright: Würth Elektronik
